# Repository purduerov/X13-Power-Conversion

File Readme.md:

# Readme for X13-Power-Conversion

Whenever you make a new part, download the datasheet and save it here _**and**_ with the part in the parts library

Always pull other people's changes before beginning to work
`git pull`

Be sure to push your changes after  working on them. Run:
1. `git add .` to add any files in this directory or a subdirectory
or `git add -u` to add any modified files
2. (Optional) `git clean -nX` to see what ignored files can be removed
	`git clean -fX` removes ignored files (Eagle backups)
3. `git commit -m "helpful commit message"` with a description of the work that you did
4. `git push` to push your work to github

Other helpful commands
* `git status` says information about modified and staged files
* `git log` shows the recent commits of the repository
* `git log filename.extension` show the recent commits for just that file
* `git checkout first-couple-letter-of-commit-id` lets you go back to a previous version
* `git checkout master` brings you back to the latest commit
* `git tag` lists the tags
* `git tag -a orderX -m "the version of the board placed for the X'th order"` tag a specific commit
* `git push --tags` needed to push tags to remote
* `git show orderX` show the commit log for the given tag
* `git checkout orderX` go back and interact with the files at the tagged commit

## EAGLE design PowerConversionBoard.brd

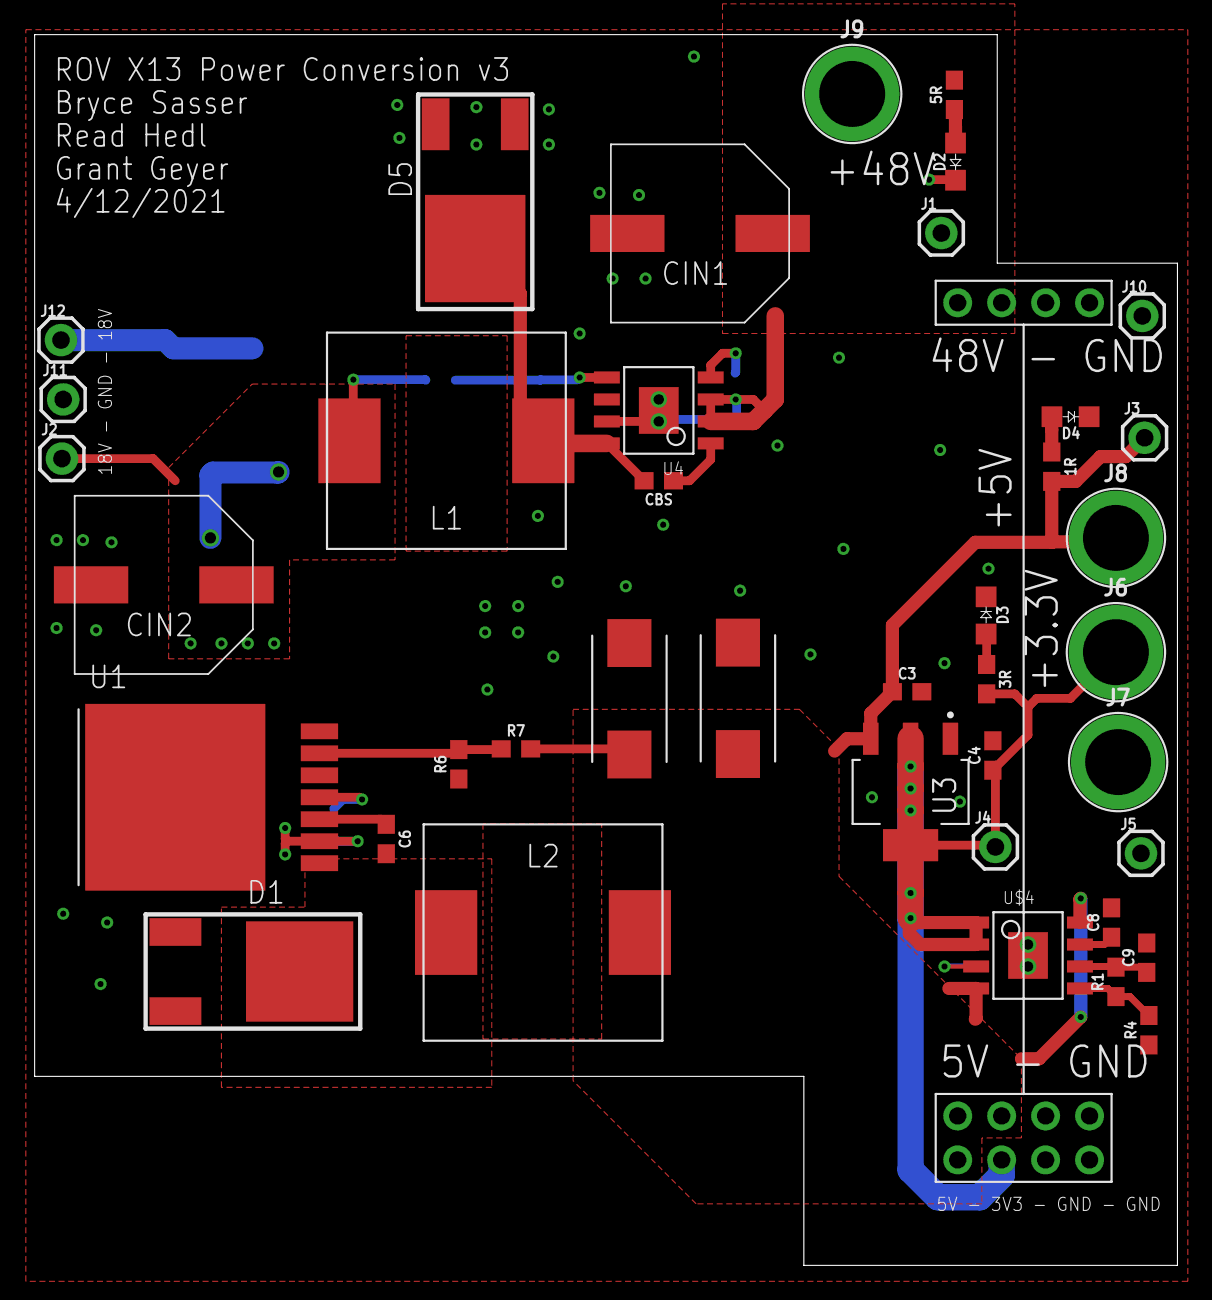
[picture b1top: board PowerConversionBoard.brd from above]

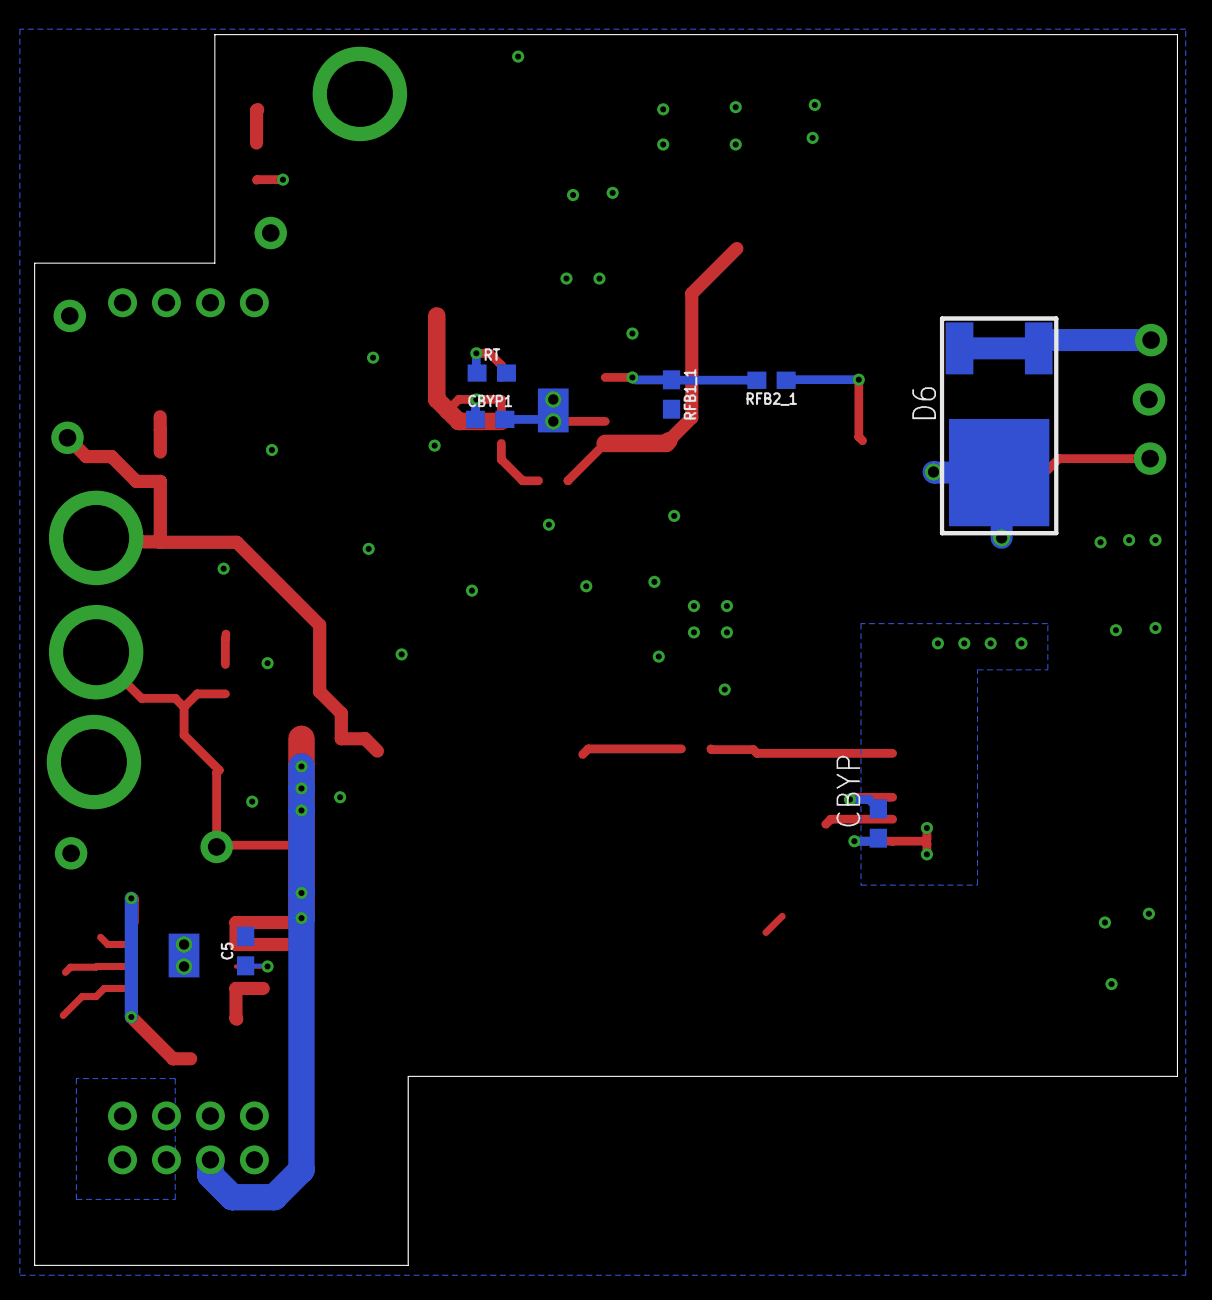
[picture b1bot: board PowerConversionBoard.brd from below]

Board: 2 copper layers, 66.0 x 71.1 mm, 48 parts (7 on the bottom side), 20 nets.

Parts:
1R, 3R: 470; 0603
5R: 5k; 0603
C3, C4: 4.7uF; 0603
C5, C8, C9: 1.0uF; 0603
C6: 10nF; 0603
CBS: 0.1uF; 0603
CBYP, CBYP1: 1uF; 0603
CIN1: 100uF; CAPAE1030X1050N
CIN2: 47uF; CAPAE1030X1050N
COUT1_2, COUT2_2: 150uF; CTAN(7.30_4.30MM)
D1, D5, D6: SWITCHMODE_SCHOTTKY; DPAK-3
D2, D3, D4: COLOR; 0805
J1, J2, J3, J4, J5, J10, J11, J12: 1X01
J6, J7, J8, J9: BANANA_CONN_NO_THERM
L1: 47uH; HCMA1305
L2: 15uH; HCMA1305
R1, R4: 0603
R6: 10k; 0603
R7: 33k; 0603
RFB1_1: 10k; 0603
RFB2_1: 230k; 0603
RT: 49.9k; 0603
U1: LM2678; D2PAK/TO-263
U3: AZ1117EH-3.3TRG1; SOT230P700X180-4N
U4: 8-SOIC-EP
U$3: CON2DIST
U$4: ADP7159ARDZ-04-R7; 8-SOIC-EP

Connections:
3V3: 3R.2, C4.1, J4.1, J6.1, U3.2, U3.4, U$3.4, U$4.1, U$4.2
5V: 1R.2, C3.1, COUT1_2.+, COUT2_2.+, J3.1, J8.1, L2.2, R7.2, U3.3, U$3.3@1, U$3.3@2, U$3.3@3, U$4.4, U$4.8
18V: CBYP.1, CIN2.+, D6.4, J2.1, L1.2, RFB2_1.1, U1.2
18V_EXT: D6.1, D6.3, J12.1
48V: 5R.2, CBYP1.1, CIN1.+, J1.1, J9.1, U4.2, U4.3, U$3.1@1, U$3.1@2
BOOTSTRAP: CBS.1, U4.1
BST: C6.1, U1.3
BYP: C5.1, U$4.3
FB1: RFB1_1.1, RFB2_1.2, U4.5
FB2: R6.2, R7.1, U1.6
GND: C3.2, C4.2, C5.2, C8.2, C9.2, CBYP.2, CBYP1.2, CIN1.-, CIN2.-, COUT1_2.-, COUT2_2.-, D1.1, D1.3, D2.C, D3.C, D4.C, D5.1, D5.3, J5.1, J7.1, J10.1, J11.1, R4.1, R6.1, RFB1_1.2, RT.2, U1.4, U1.TAB, U3.1, U4.7, U4.PAD, U4.PAD_BOT, U4.PAD_VIA1, U4.PAD_VIA2, U$3.2@1, U$3.2@2, U$3.5@1, U$3.5@2, U$3.5@3, U$3.5@4, U$4.PAD, U$4.PAD_BOT, U$4.PAD_VIA1, U$4.PAD_VIA2
unnamed: 5R.1, D2.A
unnamed: 3R.1, D3.A
unnamed: 1R.1, D4.A
REF: C9.1, R1.2, U$4.6
REF_SENSE: R1.1, R4.2, U$4.5
RT: RT.1, U4.4
SWITCH1: CBS.2, D5.4, L1.1, U4.8
SWITCH2: C6.2, D1.4, L2.1, U1.1
VREG: C8.1, U$4.7

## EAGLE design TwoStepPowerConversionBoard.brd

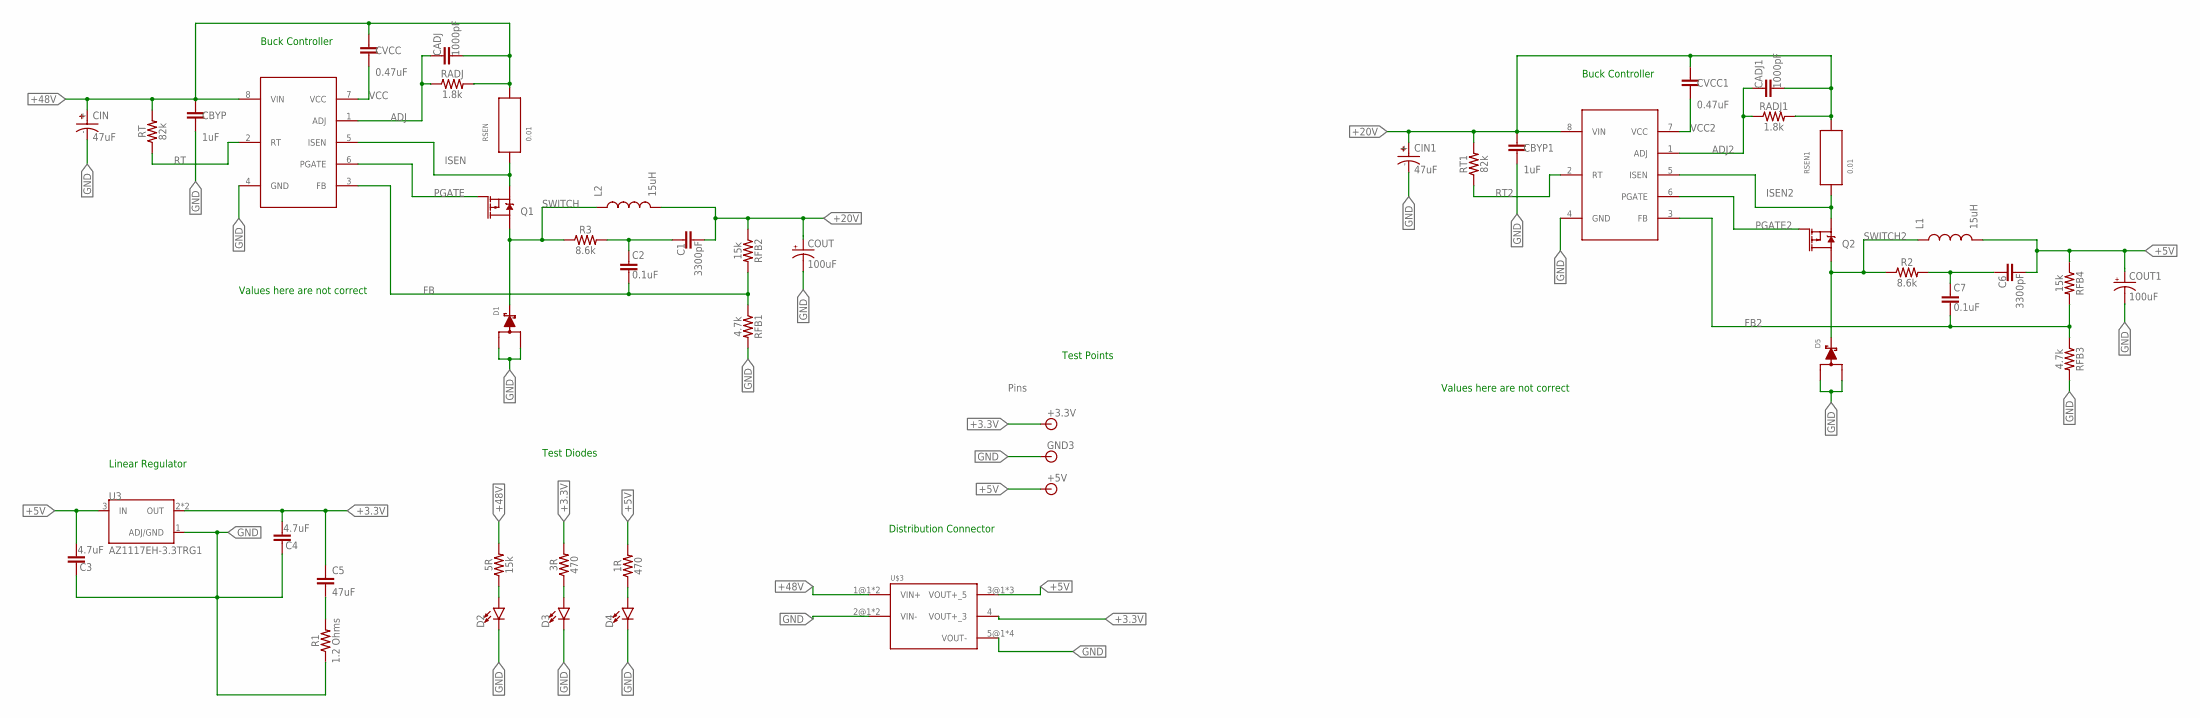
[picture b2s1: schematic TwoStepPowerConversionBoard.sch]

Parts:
1R, 3R: 470; 0603
5R: 15k; 0603
+3.3V, +5V: BANANA_CONN
C1, C6: 3300pF; 0603
C2, C7: 0.1uF; 0603
C3, C4: 4.7uF; 0603
C5: 47uF; 0603
CADJ, CADJ1: 1000pF; 0603
CBYP, CBYP1: 1uF; 0603
CIN, CIN1: 47uF; CAPAE1030X1050N
COUT, COUT1: 100uF; CTAN(7.30_4.30MM)
CVCC, CVCC1: 0.47uF; 0603
D1, D5: SWITCHMODE_SCHOTTKY; DPAK-3
D2, D3, D4: LED0603; LED-0603
GND3: BANANA_CONN
L1, L2: 15uH; HCMA1305
Q1, Q2: MOSFET_PCH-NDS8434; SO08
R1: 1.2 Ohms; 0603
R2, R3: 8.6k; 0603
RADJ, RADJ1: 1.8k; 0603
RFB1, RFB3: 4.7k; 0603
RFB2, RFB4: 15k; 0603
RSEN, RSEN1: 0.01; CSS2H-2512
RT, RT1: 82k; 0603
U3: AZ1117EH-3.3TRG1; SOT230P700X180-4N
U$1, U$2: LM5085
U$3: CON2DIST

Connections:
+3.3V: 3R.2, +3.3V.P$1, C4.1, C5.1, U3.2 (OUT), U3.4 (OUT), U$3.4 (VOUT+_3)
+5V: 1R.2, +5V.P$1, C3.1, C6.1, COUT1.+, L1.2, RFB4.1, U3.3 (IN), U$3.3@1 (VOUT+_5), U$3.3@2 (VOUT+_5), U$3.3@3 (VOUT+_5)
+20V: C1.1, CADJ1.2, CBYP1.1, CIN1.+, COUT.+, CVCC1.1, L2.2, RADJ1.2, RFB2.1, RSEN1.2, RT1.2, U$2.8 (VIN)
+48V: 5R.2, CADJ.2, CBYP.1, CIN.+, CVCC.1, RADJ.2, RSEN.2, RT.2, U$1.8 (VIN), U$3.1@1 (VIN+), U$3.1@2 (VIN+)
ADJ: CADJ.1, RADJ.1, U$1.1 (ADJ)
ADJ2: CADJ1.1, RADJ1.1, U$2.1 (ADJ)
FB: C2.2, RFB1.1, RFB2.2, U$1.3 (FB)
FB2: C7.2, RFB3.1, RFB4.2, U$2.3 (FB)
GND: C3.2, C4.2, CBYP.2, CBYP1.2, CIN.-, CIN1.-, COUT.-, COUT1.-, D1.1 (A), D1.3 (A), D2.C, D3.C, D4.C, D5.1 (A), D5.3 (A), GND3.P$1, R1.1, RFB1.2, RFB3.2, U3.1 (ADJ/GND), U$1.4 (GND), U$2.4 (GND), U$3.2@1 (VIN-), U$3.2@2 (VIN-), U$3.5@1 (VOUT-), U$3.5@2 (VOUT-), U$3.5@3 (VOUT-), U$3.5@4 (VOUT-)
ISEN: Q1.1 (S), Q1.2 (S), Q1.3 (S), RSEN.1, U$1.5 (ISEN)
ISEN2: Q2.1 (S), Q2.2 (S), Q2.3 (S), RSEN1.1, U$2.5 (ISEN)
unnamed: C6.2, C7.1, R2.2
unnamed: 5R.1, D2.A
unnamed: 3R.1, D3.A
unnamed: 1R.1, D4.A
unnamed: C1.2, C2.1, R3.2
unnamed: C5.2, R1.2
PGATE: Q1.4 (G), U$1.6 (PGATE)
PGATE2: Q2.4 (G), U$2.6 (PGATE)
RT: RT.1, U$1.2 (RT)
RT2: RT1.1, U$2.2 (RT)
SWITCH: D1.4 (C), L2.1, Q1.5 (D), Q1.6 (D), Q1.7 (D), Q1.8 (D), R3.1
SWITCH2: D5.4 (C), L1.1, Q2.5 (D), Q2.6 (D), Q2.7 (D), Q2.8 (D), R2.1
VCC: CVCC.2, U$1.7 (VCC)
VCC2: CVCC1.2, U$2.7 (VCC)

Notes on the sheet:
Pins
Linear Regulator
Buck Controller
Test Diodes
Test Points
Distribution Connector
Values here are not correct

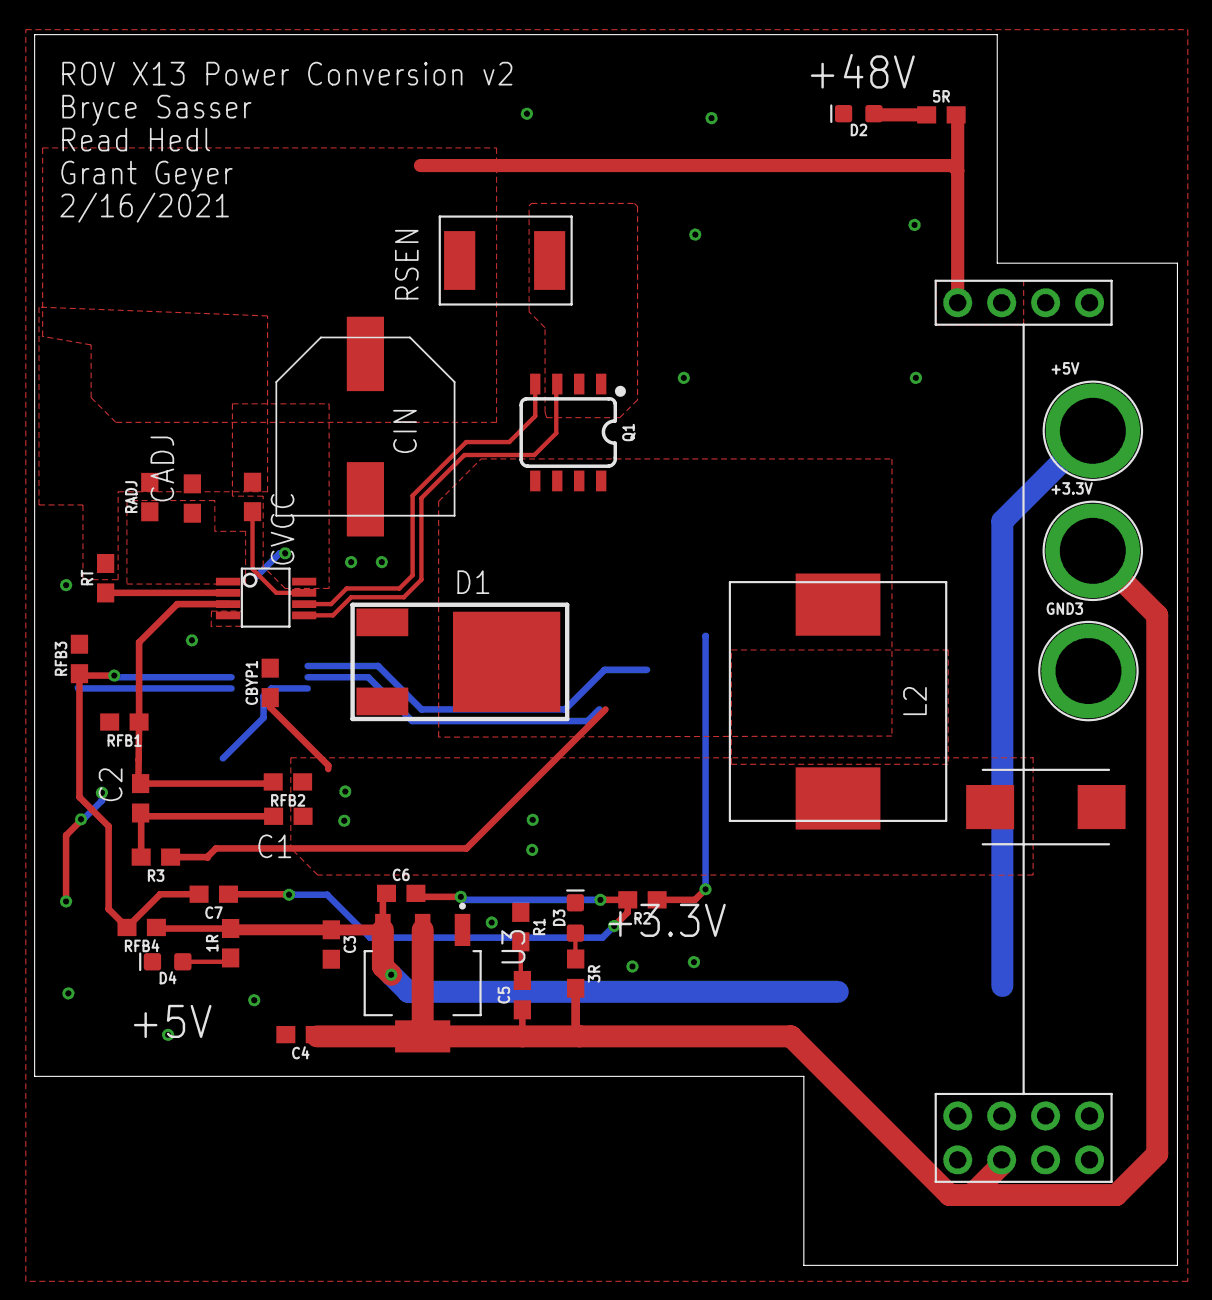
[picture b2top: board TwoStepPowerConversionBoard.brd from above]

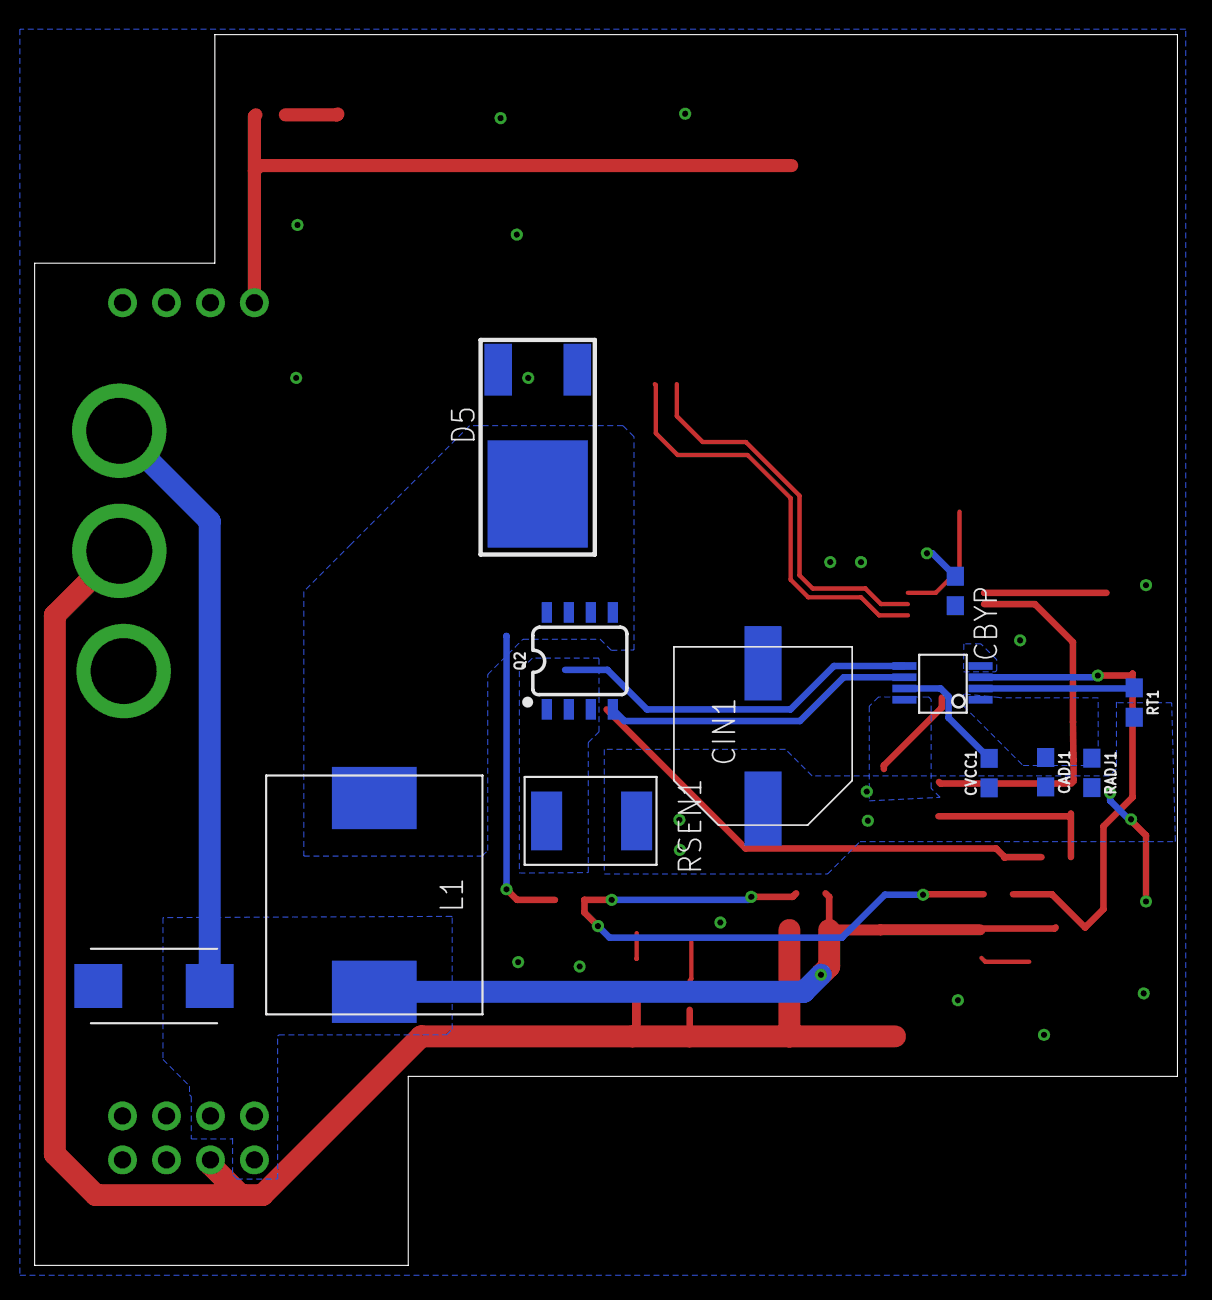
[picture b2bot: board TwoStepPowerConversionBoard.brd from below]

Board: 2 copper layers, 66.0 x 71.1 mm, 49 parts (12 on the bottom side), 25 nets.

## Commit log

2020-09-18 setup of repo
2020-10-17 Updated the old board for 48V and added the new voltage regulator; still need to include connector to power distribution
2020-10-17 added the power ditribution connector
2020-10-25 Align schematic to 0.1 in. Create board with dimension
2020-10-31 Added the connector to the distribution board
2020-11-14 made progress on the buck controller supporting circuitry
2020-11-16 threw the pieces onto the board in no particular order and finsihed the skeleton of the circuit around the buck controller. Still need to get the standard values for the inductors and capacitors, but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
2020-12-05 Changed Buck Controller output to 5.2V (did not change net label); added RC Circuit to Linear regulator; added connection to distribution board
2020-12-05 Copied in last year's capacitor and inductor
2020-12-05 copied old parts over
2020-12-05 routed the board
2020-12-05 wrong inductor previously. oops
2020-12-05 routed everything (except ground) hopefully right
2020-12-05 Finished all the routing
2020-12-06 Fixed an air wire I missed earlier
2020-12-06 Fixed it for real this time\
2021-01-03 Fixed wire sizing and some of the angles on the board
2021-01-05 Rough draft of the new and improved board finished; need to work out wires connecting to polygons and probably clean up the test points; there are also a few strange wiring places that need to be cle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
2021-01-06 Pretty much finished the layput of the board, but a few minor changes still need to be made; awaiting dimensions of potential cutoffs
2021-01-07 smaller board outline
2021-01-07 Renamed the nets and inceased wire size where it was reasonable. Also moved around some components for strighter wiring.
2021-01-10 Finished the board and added the text
2021-01-10 Cleaning up git and adding exports for ordering
2021-01-11 playing with 3d models generated by eagle package
2021-02-17 Reeeeeeeeeev 2 on the red line
2021-02-17 Finished mapping the board for the two step process. The correct values are not calculated for either step of the conversion.
2021-02-17 Larger LEDs on main and graphic and text on the other
2021-04-13 V3 with buck converter of previous years

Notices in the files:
parts and their libraries:
SparkFun-Connectors: Licensing: Creative Commons ShareAlike 4.0 International - https://creativecommons.org/licenses/by-sa/4.0
